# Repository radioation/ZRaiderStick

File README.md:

**_IMPORTANT_**: This is still a work in progress. 

# Z Raider Stick
Z Raider - Analog Joystick for Atari 800/XL/XE Computers

Just a nigh-useless analog joystick project for Atari 8-bit computers. It's meant to 
work with my [port](https://github.com/radioation/StarRaidersMods) of the Atari 5200 
Star Raiders analog controls to the 8-bit version. 

Z Raider may work with other Atari consoles but I've not tested this. I've done
a little work with the C64, but it is nowhere near working. The current arduino
code will absolutely _NOT_ work with the C64.

My work is largely based on:
* Jeff Piepmeier's [Atari POKEY Actuation with Arduino](https://jeffpiepmeier.blogspot.com/2020/02/atari-pokey-actuation-with-arduino.html) blog post. My initial tests followed this pretty closesly. He doesn't state which diode he used. So I tried a few that I had on hand and the 1N4001 worked pretty well. Unfortunately, I was having a hard time getting stable values for two axis. A single axis using delays worked well. Adding a second axis introduced jitter. Most likely due to the way I was tracking the pulse delays.
* Danjovic's [Stingray](https://github.com/Danjovic/Stingray). This is Nintendo Classic controller adapter with keypad emulation for the Atari 5200. This project handled the pulse delays in using the Arduino UNO's TIMER2 interrupt to approximate delays for each horizontal line. Using this technique gives much better results than my use of total delay time checked by loop().

# Circuit
**_IMPORTANT_: Any circuits in this project are experimental. I am not a practicing electrical engineer. The circuit diagrams I put (will put) here are what I've tested on my Ataris. The circuits work for me, but I'm _not_ an expert at hardware design. It's possible that I'm doing something incorrectly that may damage the computer. USE THIS PROJECT AT YOUR OWN RISK**

* Arduino UNO R3 or Nano V3. I've tested on Elegoo clones.
* D1, D2 - 1N4001 Diode
* D3 - 1N5817 Schottky Diode
* R1 - 100 Ohm
* R2,R3 - 330 Ohm
* R4 - 2.7 kOhm ( I used 2.2k + 560 ~= 2.76kOhm. The main thing is to get a voltage divider in this range for the comparator )
* R5 - 10 kOhm
* C1,C2 - 100 nF
* S1B, S1C - 10 kOhm ( basic thumbstick, I'm currently looking at RKJXV1224005 thumbsticks in KiCAD )
* F1 - Polyfuse 100mA (Optional. Can use 0 Ohm)
* 6 push button switches

## Atari 800/XL/XE Schematic:

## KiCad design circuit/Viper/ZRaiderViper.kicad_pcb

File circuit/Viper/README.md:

DOn't use this yet. Still working through it"

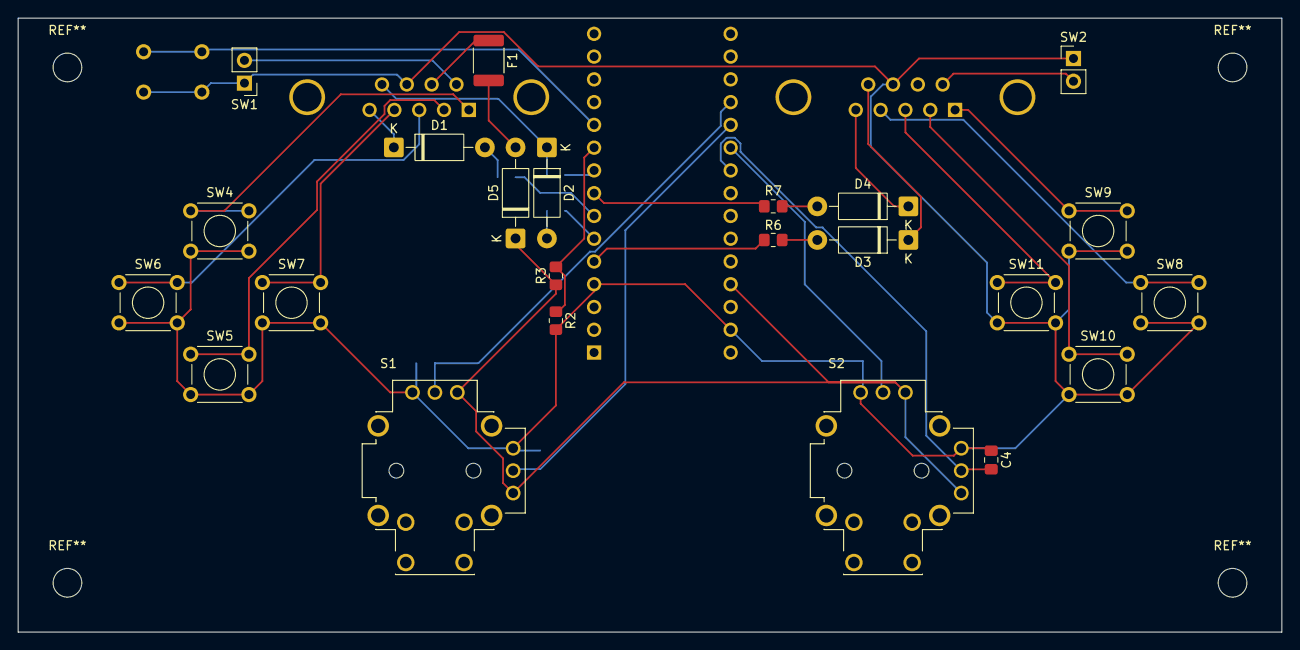
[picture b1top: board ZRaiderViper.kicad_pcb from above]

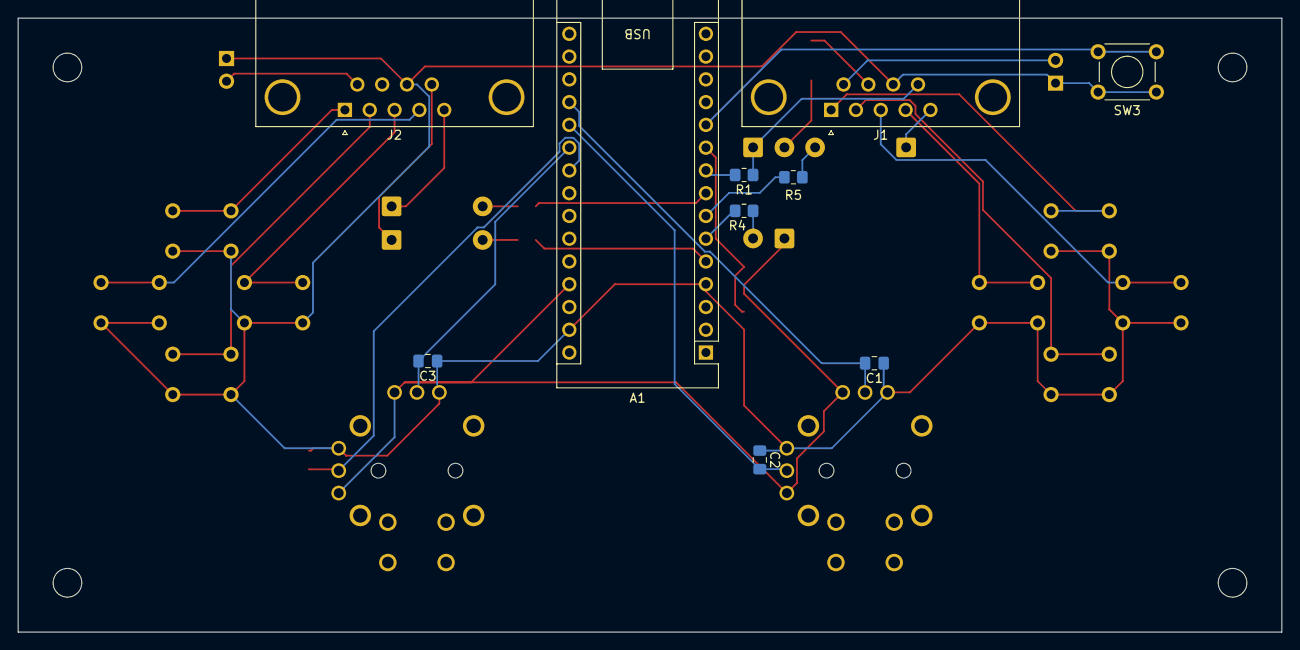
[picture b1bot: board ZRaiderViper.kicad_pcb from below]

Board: 2 copper layers, 141.0 x 68.5 mm, 33 parts (10 on the bottom side), 33 nets.

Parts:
A1: Arduino_Nano_v3.x; Arduino_Nano
C1, C2, C3, C4: 100 nF; C_0805_2012Metric_Pad1.18x1.45mm_HandSolder
D1, D2, D3, D4: 1N4001; D_DO-41_SOD81_P10.16mm_Horizontal
D5: 1N5817; D_DO-41_SOD81_P10.16mm_Horizontal
F1: 100MA; Fuse_1812_4532Metric_Pad1.30x3.40mm_HandSolder
J1, J2: DE9_Socket; DSUB-9_Socket_Horizontal_P2.77x2.84mm_EdgePinOffset9.90mm_H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
R1: 100; R_0805_2012Metric_Pad1.20x1.40mm_HandSolder
R2: 10k; R_0805_2012Metric_Pad1.20x1.40mm_HandSolder
R3: 2.7k; R_0805_2012Metric_Pad1.20x1.40mm_HandSolder
R4, R5, R6, R7: 330; R_0805_2012Metric_Pad1.20x1.40mm_HandSolder
S1, S2: RKJXV122400R; SW_RKJXV122400R
SW1: TRIGGER_1; PinHeader_1x02_P2.54mm_Vertical
SW2: TRIGGER_2; PinHeader_1x02_P2.54mm_Vertical
SW3: Calibrate; SW_TH_Tactile_Omron_B3F-100x
SW4: UP_1; SW_TH_Tactile_Omron_B3F-100x
SW5: DOWN_1; SW_TH_Tactile_Omron_B3F-100x
SW6: LEFT_1; SW_TH_Tactile_Omron_B3F-100x
SW7: RIGHT_1; SW_TH_Tactile_Omron_B3F-100x
SW8: RIGHT_2; SW_TH_Tactile_Omron_B3F-100x
SW9: UP_2; SW_TH_Tactile_Omron_B3F-100x
SW10: DOWN_2; SW_TH_Tactile_Omron_B3F-100x
SW11: LEFT_2; SW_TH_Tactile_Omron_B3F-100x

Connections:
unnamed: A1.27 (+5V), D5.1 (K), R3.1, S1.VR1_1, S1.VR2_1, S2.VR1_1, S2.VR2_1
unnamed: A1.19 (A0), C1.2, S1.VR2_2
unnamed: A1.20 (A1), C2.2, S1.VR1_2
unnamed: A1.21 (A2), C3.2, S2.VR2_2
unnamed: A1.22 (A3), C4.2, S2.VR1_2
unnamed: A1.5 (D2), R6.1
unnamed: A1.6 (D3), R4.2
unnamed: A1.7 (D4), R5.1
unnamed: A1.8 (D5), R7.2
unnamed: A1.9 (D6), R1.2
unnamed: A1.10 (D7), R2.1, R3.2
unnamed: A1.11 (D8), SW3.2
unnamed: A1.4 (GND), A1.29 (GND), C1.1, C2.1, C3.1, C4.1, J1.8, J2.8, R2.2, S1.VR1_3, S1.VR2_3, S2.VR1_3, S2.VR2_3, SW1.1, SW2.1, SW3.1, SW4.2, SW5.2, SW6.2, SW7.2, SW8.2, SW9.2, SW10.2, SW11.2
unnamed: D1.2 (A), R5.2
unnamed: D1.1 (K), J1.5
unnamed: D2.2 (A), R4.1
unnamed: D2.1 (K), J1.9, R1.1
unnamed: D3.2 (A), R6.2
unnamed: D3.1 (K), J2.9
unnamed: D4.2 (A), R7.1
unnamed: D4.1 (K), J2.5
unnamed: D5.2 (A), F1.2
unnamed: F1.1, J1.7
unnamed: J1.1, SW4.1
unnamed: J1.2, SW5.1
unnamed: J1.3, SW6.1
unnamed: J1.4, SW7.1
unnamed: J1.6, SW1.2
unnamed: J2.1, SW9.1
unnamed: J2.2, SW10.1
unnamed: J2.3, SW11.1
unnamed: J2.4, SW8.1
unnamed: J2.6, SW2.2

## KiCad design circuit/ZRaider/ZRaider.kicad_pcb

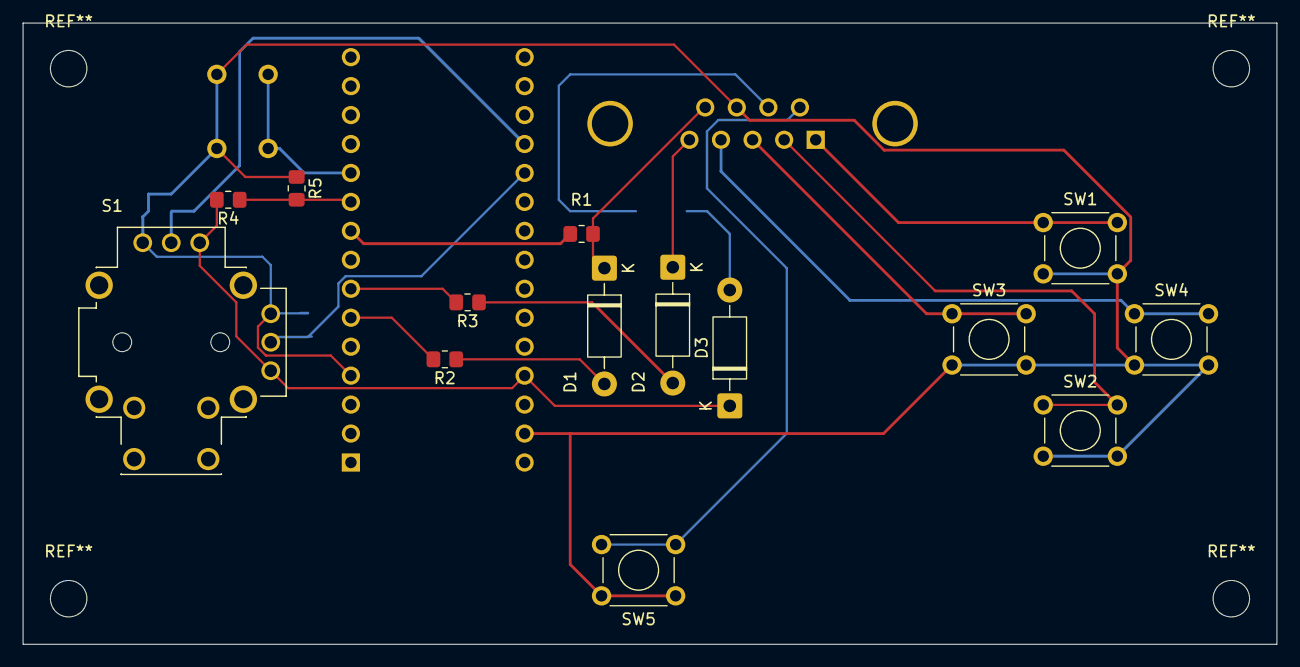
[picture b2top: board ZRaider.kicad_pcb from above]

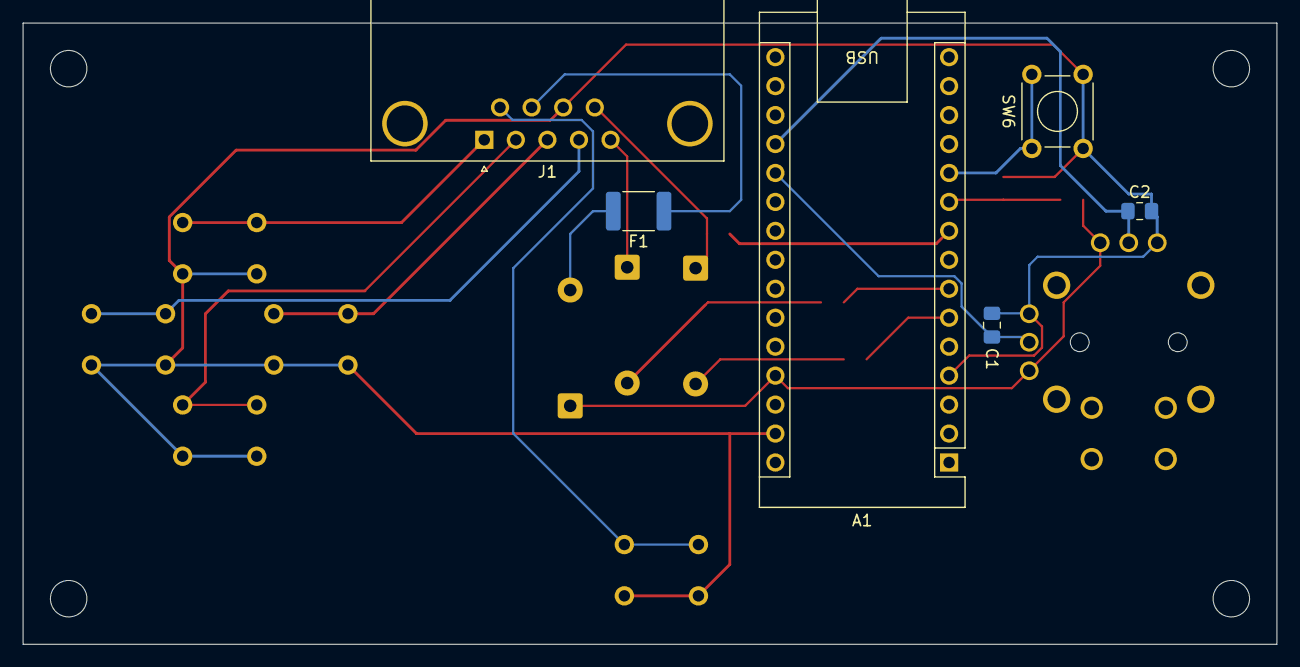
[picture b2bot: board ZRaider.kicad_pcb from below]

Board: 2 copper layers, 110.0 x 54.5 mm, 20 parts (6 on the bottom side), 19 nets.

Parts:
A1: Arduino_Nano_v3.x; Arduino_Nano
C1, C2: 100 nF; C_0805_2012Metric_Pad1.18x1.45mm_HandSolder
D1, D2: 1N4001; D_DO-41_SOD81_P10.16mm_Horizontal
D3: 1N5817; D_DO-41_SOD81_P10.16mm_Horizontal
F1: 100MA; Fuse_1812_4532Metric_Pad1.30x3.40mm_HandSolder
J1: DE9_Socket; DSUB-9_Socket_Horizontal_P2.77x2.84mm_EdgePinOffset9.90mm_H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
R1: 100; R_0805_2012Metric_Pad1.20x1.40mm_HandSolder
R2, R3: 330; R_0805_2012Metric_Pad1.20x1.40mm_HandSolder
R4: 2.7k; R_0805_2012Metric_Pad1.20x1.40mm_HandSolder
R5: 10k; R_0805_2012Metric_Pad1.20x1.40mm_HandSolder
S1: RKJXV122400R; SW_RKJXV122400R
SW1: UP; SW_TH_Tactile_Omron_B3F-100x
SW2: DOWN; SW_TH_Tactile_Omron_B3F-100x
SW3: LEFT; SW_TH_Tactile_Omron_B3F-100x
SW4: RIGHT; SW_TH_Tactile_Omron_B3F-100x
SW5: Trigger; SW_TH_Tactile_Omron_B3F-100x
SW6: Calibrate; SW_TH_Tactile_Omron_B3F-100x

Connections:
unnamed: A1.27 (+5V), D3.1 (K), R4.2, S1.VR1_1, S1.VR2_1
unnamed: A1.19 (A0), C2.1, S1.VR2_2
unnamed: A1.20 (A1), C1.2, S1.VR1_2
unnamed: A1.6 (D3), R2.2
unnamed: A1.7 (D4), R3.2
unnamed: A1.9 (D6), R1.2
unnamed: A1.11 (D8), SW6.1
unnamed: A1.4 (GND), A1.29 (GND), C1.1, C2.2, J1.8, R5.1, S1.VR1_3, S1.VR2_3, SW1.2, SW2.2, SW3.2, SW4.2, SW5.1, SW6.2
unnamed: D1.2 (A), R2.1
unnamed: D1.1 (K), J1.9, R1.1
unnamed: D2.2 (A), R3.1
unnamed: D2.1 (K), J1.5
unnamed: D3.2 (A), F1.2
unnamed: F1.1, J1.7
unnamed: J1.1, SW1.1
unnamed: J1.2, SW2.1
unnamed: J1.3, SW3.1
unnamed: J1.4, SW4.1
unnamed: J1.6, SW5.2
